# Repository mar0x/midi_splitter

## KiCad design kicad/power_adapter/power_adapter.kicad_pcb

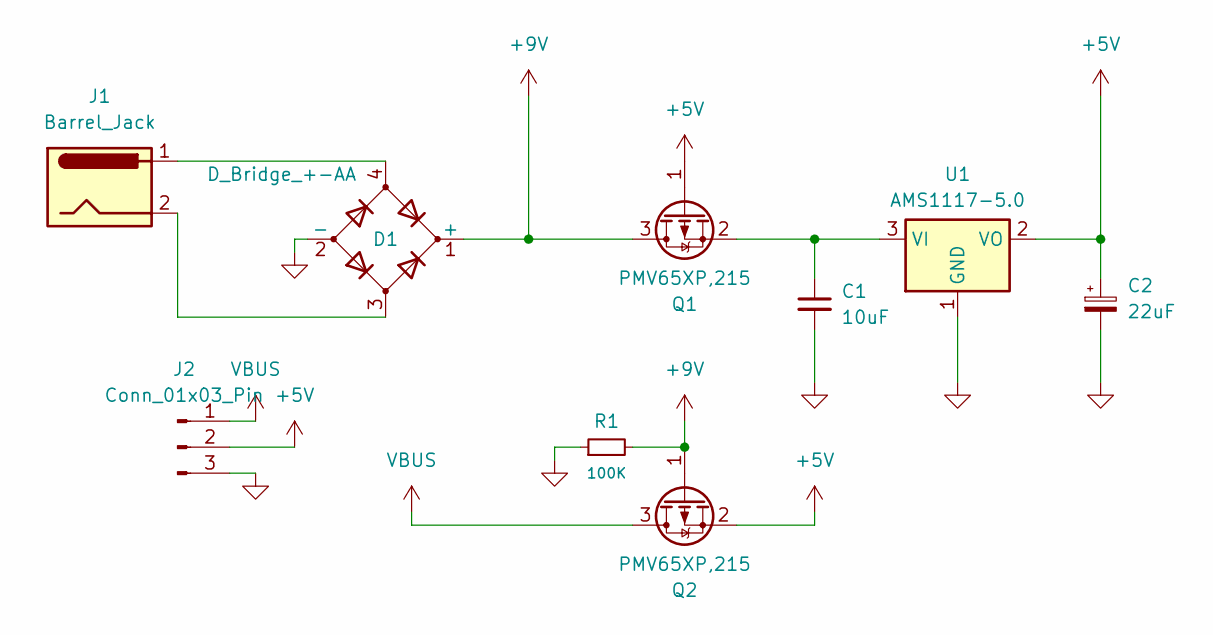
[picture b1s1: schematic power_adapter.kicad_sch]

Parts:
C1: 10uF; C_0805_2012Metric
C2: 22uF; CP_EIA-3528-21_Kemet-B
D1: D_Bridge_+-AA; Diode_Bridge_MBS
J1: Barrel_Jack; BarrelJack_Wuerth_6941xx301002
J2: Conn_01x03_Pin; PinHeader_1x03_P2.00mm_Vertical
Q1, Q2: PMV65XP,215; SOT-23
R1: 100K; R_0805_2012Metric
U1: AMS1117-5.0; SOT-223-3_TabPin2

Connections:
+5V: C2.1, J2.2, Q1.1 (G), Q2.2 (S), U1.2 (VO)
+9V: D1.1 (+), Q1.3 (D), Q2.1 (G), R1.2
GND: C1.2, C2.2, D1.2 (-), J2.3, R1.1, U1.1 (GND)
unnamed: D1.3, J1.2
unnamed: D1.4, J1.1
unnamed: C1.1, Q1.2 (S), U1.3 (VI)
VBUS: J2.1, Q2.3 (D)

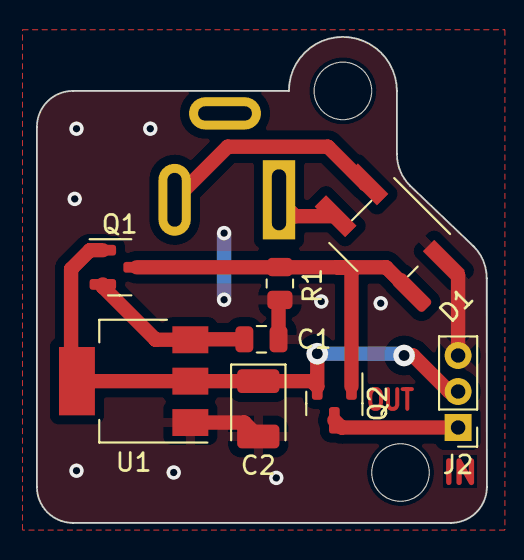
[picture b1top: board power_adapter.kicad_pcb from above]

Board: 2 copper layers, 25.0 x 27.0 mm, 9 parts (1 on the bottom side), 7 nets.

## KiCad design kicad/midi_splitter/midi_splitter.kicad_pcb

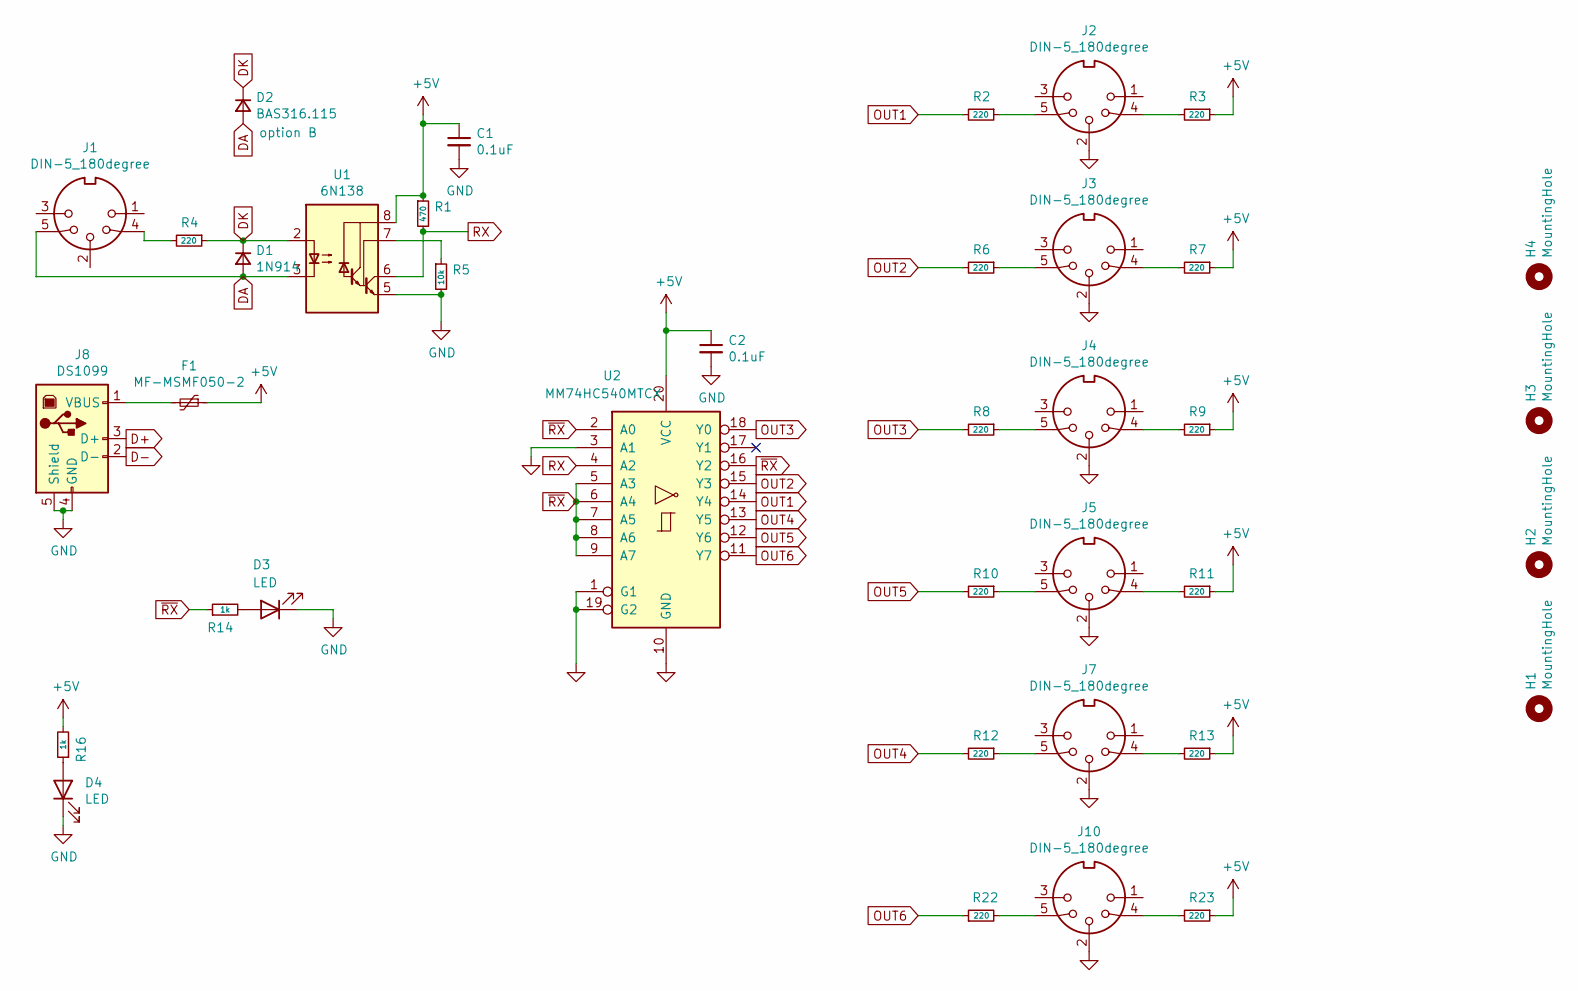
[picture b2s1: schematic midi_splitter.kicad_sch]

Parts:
C1, C2: 0.1uF; C_0805_2012Metric_Pad1.15x1.40mm_HandSolder
D1: 1N914; D_DO-34_SOD68_P7.62mm_Horizontal
D2: BAS316.115; D_SOD-323_HandSoldering
D3: LED; LED_D3.0mm_Horizontal_O1.27mm_Z10.0mm
D4: LED; LED_D3.0mm_Horizontal_O1.27mm_Z6.0mm
F1: MF-MSMF050-2; Fuse_1812_4532Metric_Pad1.30x3.40mm_HandSolder
H1, H2, H3, H4: MountingHole; MountingHole_2.7mm_M2.5_ISO14580
J1, J2, J3, J4, J5, J7, J10: DIN-5_180degree; DIN5MIDI-OOTDTY
J8: DS1099; USB_B_OST_USB-B1HSxx_Horizontal
R1: 470; R_0805_2012Metric_Pad1.15x1.40mm_HandSolder
R2, R3, R4, R6, R7, R8, R9, R10, R11, R12, R13: 220; R_0805_2012Metric_Pad1.15x1.40mm_HandSolder
R5: 10k; R_0805_2012Metric_Pad1.15x1.40mm_HandSolder
R14, R16: 1k; R_0805_2012Metric_Pad1.15x1.40mm_HandSolder
R22, R23: 220; R_0805_2012Metric_Pad1.20x1.40mm_HandSolder
U1: 6N138; DIP-8_W8.89mm_SMDSocket_LongPads
U2: MM74HC540MTCX; TSSOP-20_4.4x6.5mm_P0.65mm

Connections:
+5V: C1.1, C2.1, F1.1, R1.1, R3.1, R7.1, R9.1, R11.1, R13.1, R16.2, R23.1, U1.8 (VCC), U2.20 (VCC)
D+: J8.3 (D+)
D-: J8.2 (D-)
DA: D1.2 (A), D2.2 (A), J1.5, U1.3 (C2)
DK: D1.1 (K), D2.1 (K), R4.1, U1.2 (C1)
GND: C1.2, C2.2, D3.1 (K), D4.1 (K), J2.2, J3.2, J4.2, J5.2, J7.2, J8.4 (GND), J8.5 (Shield), J10.2, R5.2, U1.5 (GND), U2.1 (G1), U2.3 (A1), U2.10 (GND), U2.19 (G2)
unnamed: D3.2 (A), R14.2
unnamed: D4.2 (A), R16.1
unnamed: F1.2, J8.1 (VBUS)
unnamed: J1.4, R4.2
unnamed: J2.4, R3.2
unnamed: J2.5, R2.1
unnamed: J3.4, R7.2
unnamed: J3.5, R6.1
unnamed: J4.4, R9.2
unnamed: J4.5, R8.1
unnamed: J5.4, R11.2
unnamed: J5.5, R10.1
unnamed: J7.4, R13.2
unnamed: J7.5, R12.1
unnamed: J10.4, R23.2
unnamed: J10.5, R22.2
unnamed: R5.1, U1.7 (VO1)
OUT1: R2.2, U2.14 (Y4)
OUT2: R6.2, U2.15 (Y3)
OUT3: R8.2, U2.18 (Y0)
OUT4: R12.2, U2.13 (Y5)
OUT5: R10.2, U2.12 (Y6)
OUT6: R22.1, U2.11 (Y7)
RX: R1.2, U1.6 (VO2), U2.4 (A2)
~RX: R14.1, U2.2 (A0), U2.5 (A3), U2.6 (A4), U2.7 (A5), U2.8 (A6), U2.9 (A7), U2.16 (Y2)

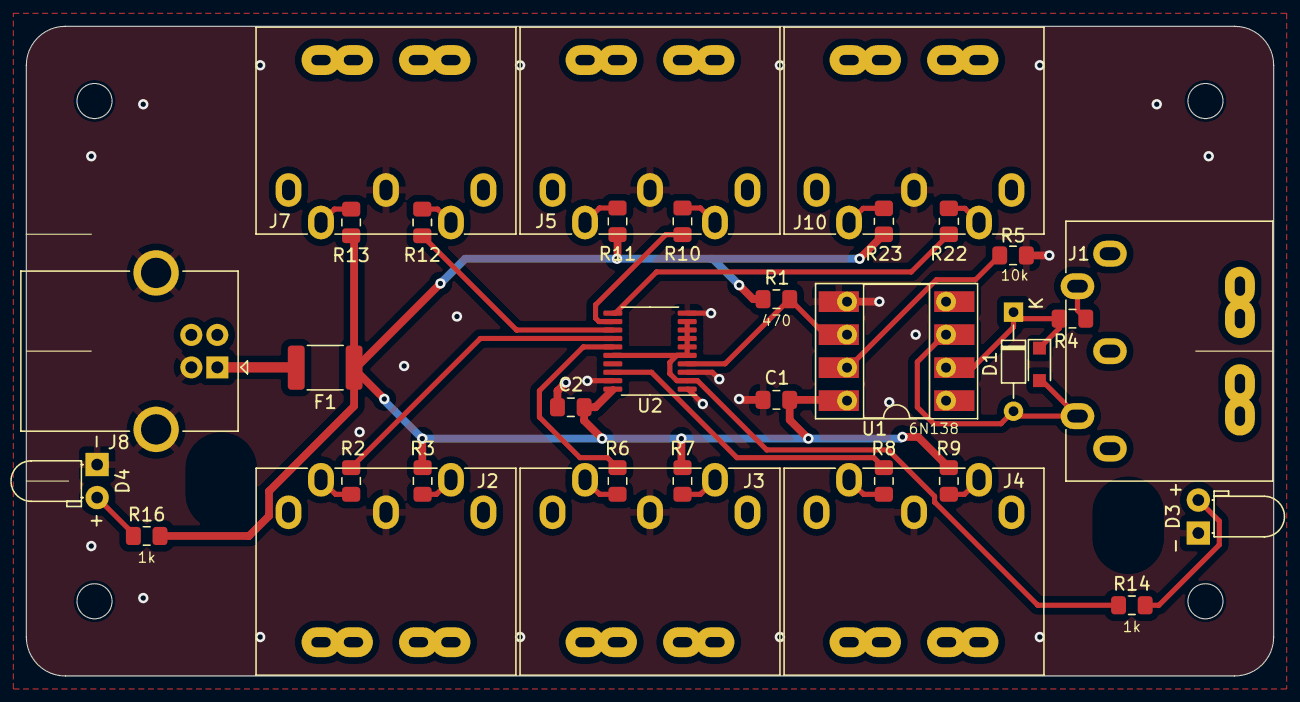
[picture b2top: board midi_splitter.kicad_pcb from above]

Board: 2 copper layers, 96.0 x 50.0 mm, 38 parts (0 on the bottom side), 29 nets.

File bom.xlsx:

id | q |  | desc | Vendor |  | Order info
 |  |  |  | URL | code | # | date | price | count | shipping | cost | cost per item
G1032BA | 1 |  | Корпус для РЭА 101х54х41.7мм, пластик, черный, алюминиевая панель | G1032BA | Z96811 | 97481 | 44069 | 121.87 | 11 | 300 | 1640.5700000000002 | 149.14272727272729
DS-210 | 1 | J6 | Гнездо питания 2,1х5,5мм на панель | DS-210 |  | 5005159492062510 | 44070 | 3.5819999999999999 | 10 | 65.42 | 101.24000000000001 | 10.124000000000001
DB102 | 1 | D2 | Диодный мост | DB102 |  | 5005159492542510 | 44070 | 4.6340000000000003 | 20 | 46.73 | 139.41 | 6.9704999999999995
L4940V5 | 0 | U3 | Регулятор 5В, 1.5А, [TO-220] | L4940V5 |  | 5005170509072510 | 44070 | 21.806000000000001 | 10 | 53.74 | 271.8 | 0
 | 1 |  |  | L4940V5 | 2453 | 7133821 | 44114 | 52.5 | 10 | 236 | 761 | 76.099999999999994
SS-16-22 | 1 | C4 | Конд.эл. 22мкф 16В 4x7мм | SS-16-22 |  |  |  | 1.6 | 10 | 0 | 16 | 1.6
1N914 | 1 | D1 | Диод 75 мА 75В 5нс [DO-35] | 1N914 | 369837539 |  |  | 3 | 10 | 0 | 30 | 3
6N138M | 1 | U1 | Оптопара с транзисторным выходом [SMD DIP-8] | 6N138M |  | 5005159492502510 | 44070 | 8.8780000000000001 | 10 | 53.74 | 142.52000000000001 | 14.252000000000001
SN74HC14N | 1 | U2 | Инвертирующий Триггер Шмитта [DIP-14] | SN74HC14N |  | 5005159492642510 | 44070 | 9.5009999999999994 | 10 | 53.74 | 148.75 | 14.875
RTW909080M | 6 | J1,J2,J3,J4,J5,J7 | DIN connector 5 Pin DIN Female Jack Right Angle Panel Mount 90 Degree | RTW909080M |  | 5005159492622510 | 44070 | 23.052 | 60 | 141.74 | 1524.86 | 152.48599999999999
PCB | 1 |  |  | JLCPCB |  |  |  | 37.35 | 10 | 566.23 | 939.73 | 93.972999999999999
220Ohm | 11 | R2,R3,R4,R6,R7,R8,R9,R10,R11,R12,R13 | 0.125Вт 0805 220 Ом, 1%, Чип резистор (SMD) |  |  |  |  | 0.50619999999999998 | 100 | 0 | 50.62 | 5.5682
470Ohm | 1 | R1 | 0.125Вт 0805 470 Ом, 1%, Чип резистор (SMD) |  |  |  |  | 0.50619999999999998 | 100 | 0 | 50.62 | 0.50619999999999998
10kOhm | 1 | R5 | 0.125Вт 0805 10 кОм, 1%, Чип резистор (SMD) |  |  |  |  | 0.50619999999999998 | 100 | 0 | 50.62 | 0.50619999999999998
1kOhm | 3 | R14,R15,R16 | 0.125Вт 0805 1 кОм, 1%, Чип резистор (SMD) |  |  |  |  | 0.50619999999999998 | 100 | 0 | 50.62 | 1.5185999999999999
0.1uF | 3 | C1,C2,C3 | Кер.ЧИП конд. 0.1 мкФ X7R 50В 10% 0805, GRM21BR71H104K | GRM21BR71H104K | 860640216 |  |  | 7 | 20 | 0 | 140 | 21
 |  |  |  |  |  |  |  |  |  |  |  | 551.62242727272735

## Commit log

2019-02-27 Adding URLs to BOM.
2019-02-27 Fixing power plug connection.
2019-03-01 Introducing images and gerber files.
2020-10-12 KiCad board added.
2020-10-17 Removing old version.
2021-01-21 Adding 6th MIDI OUT and USB power input.
2021-01-21 Updating images.
2021-12-07 Updating U4 for SN74LVC1G125.
    This closes #1 issue on GitHub.
2021-12-10 Updating U4 in generated files.
2022-03-05 Adding cover file.
2022-03-05 Updating BOM.
2022-03-23 Reducing number of components.
    - removing 9-12v power supply option;
    - replacing 74hc14 with 74hc540;
2022-03-23 Updating MIDI socket 3D model.
2022-07-08 Cover images and engraving
2022-07-08 Box makeing files
2022-07-08 Box for old x6 splitter
2022-07-23 Making box 1mm lower.
2023-10-18 Moving kicad project into directory
2023-10-18 Start version with TRS
2024-02-02 9V Power adapter board introduced
2024-02-03 Adjusting path to 3D models
2024-02-03 Upgrading to KiCAD 7
2024-02-03 Improving power adapter
2024-02-09 Power adapter fixes
2024-02-12 Automatic box probe
2024-02-12 Speed up milling, add one more power hole
